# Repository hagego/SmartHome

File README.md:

# SmartHome
Tools and applications for my simple, very heterogeneous smart home

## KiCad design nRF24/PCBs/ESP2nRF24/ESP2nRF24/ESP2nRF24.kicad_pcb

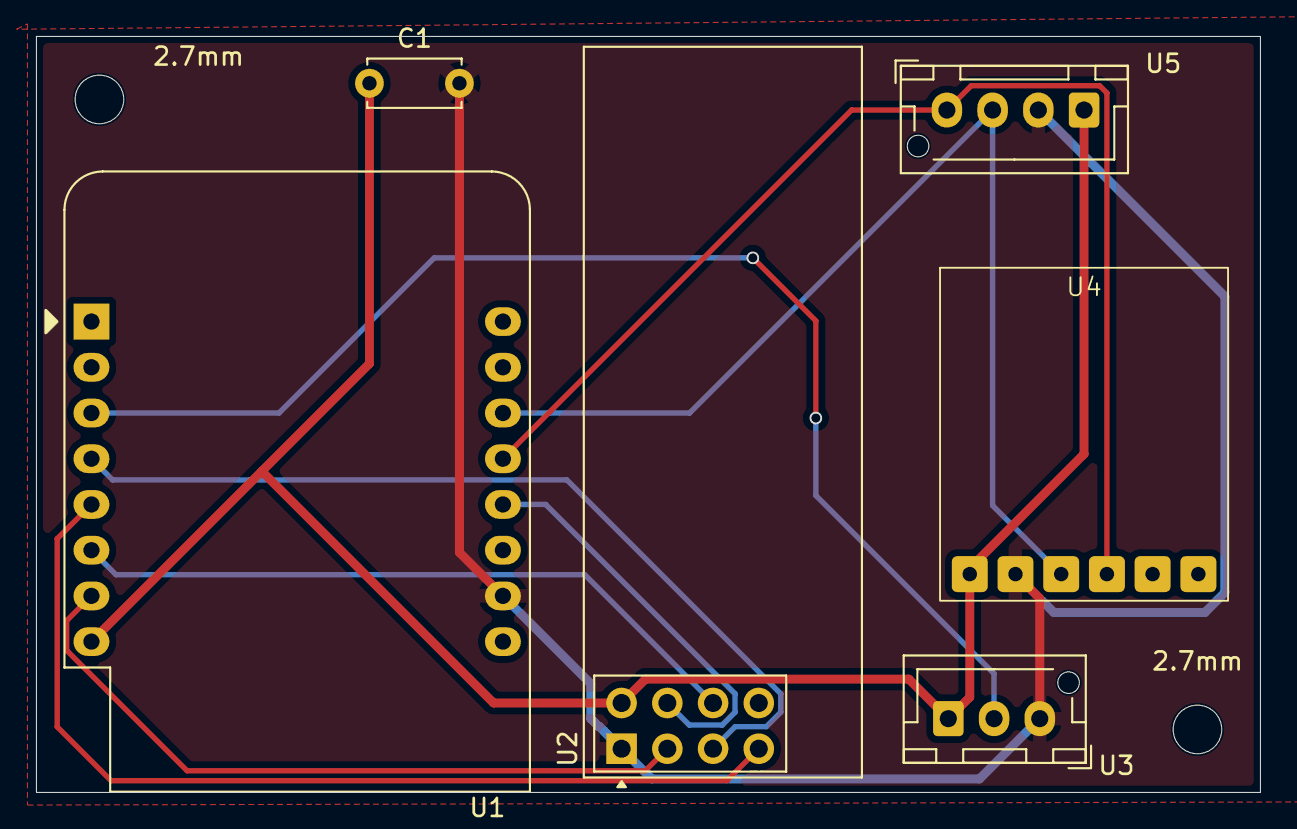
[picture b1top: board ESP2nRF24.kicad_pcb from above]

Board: 2 copper layers, 68.0 x 42.0 mm, 8 parts (0 on the bottom side), 10 nets.

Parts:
2.7mm, 2.7mm#2: MountingHole_2.7mm_M2.5
C1: 4.4uF; C_Disc_D5.0mm_W2.5mm_P5.00mm
U1: WEMOS_D1_mini; ESP8266 Mini USB-C
U2: NRF24L01_Breakout; nRF24L01_Breakout_extAntenna
U3: AM312; JST_XH_1x03_P2.54
U4: BE680; BME680
U5: BH1750; JST_XH_1x04_P2.54

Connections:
GND: C1.2, U1.10 (GND), U2.1 (GND), U3.3 (GND), U4.2 (GND), U5.2 (GND)
unnamed: C1.1, U1.8 (3V3), U2.2 (VCC), U3.1 (VCC), U4.1 (VCC), U5.1 (VCC)
unnamed: U1.7 (CS/D8), U2.3 (CE)
unnamed: U1.3 (D0), U3.2 (VOUT)
unnamed: U1.12 (D3), U2.4 (~CSN)
unnamed: U1.5 (MISO/D6), U2.7 (MISO)
unnamed: U1.6 (MOSI/D7), U2.6 (MOSI)
unnamed: U1.4 (SCK/D5), U2.5 (SCK)
unnamed: U1.14 (SCL/D1), U4.3 (SCL), U5.3 (SCL)
unnamed: U1.13 (SDA/D2), U4.4 (SDA), U5.4 (SDA)

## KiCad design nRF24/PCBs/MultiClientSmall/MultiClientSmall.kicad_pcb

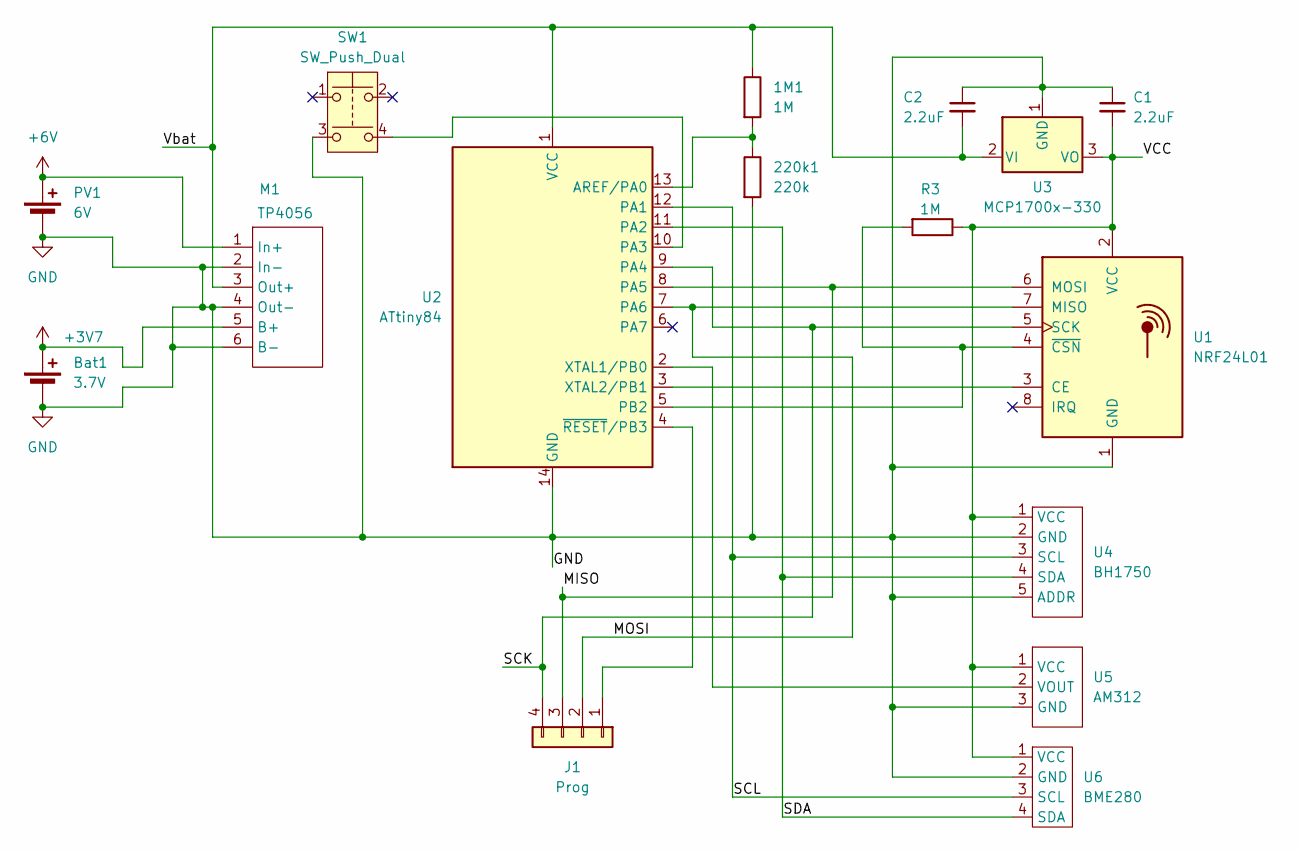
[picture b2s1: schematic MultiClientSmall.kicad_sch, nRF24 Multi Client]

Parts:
1M1: 1M; R_Axial_DIN0207_L6.3mm_D2.5mm_P10.16mm_Horizontal
220k1: 220k; R_Axial_DIN0207_L6.3mm_D2.5mm_P10.16mm_Horizontal
Bat1: 3.7V; JST_PH_1x02_P2.00
C1, C2: 2.2uF; C_Disc_D5.0mm_W2.5mm_P5.00mm
J1: Prog; PinHeader_1x04_P2.54mm_Vertical
M1: TP4056; TP4056-18650
PV1: 6V; JST_PH_1x02_P2.00
R3: 1M; R_Axial_DIN0207_L6.3mm_D2.5mm_P10.16mm_Horizontal
SW1: SW_Push_Dual; Push_E-Switch_KS01Q01
U1: NRF24L01; nRF24L01_Breakout
U2: ATtiny84; DIP-14_W7.62mm_Socket
U3: MCP1700x-330; TO-92_HandSolder
U4: BH1750
U5: AM312
U6: BME280

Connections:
+3V7: Bat1.1 (+), M1.5 (B+)
+6V: M1.1 (In+), PV1.1 (+)
/MISO: J1.3, U1.6 (MOSI), U2.8 (PA5)
/MOSI: J1.2, U1.7 (MISO), U2.7 (PA6)
/SCK: J1.4, U1.5 (SCK), U2.9 (PA4)
/SCL: U2.12 (PA1), U4.3 (SCL), U6.3 (SCL)
/SDA: U2.11 (PA2), U4.4 (SDA), U6.4 (SDA)
/VCC: C1.2, R3.1, U1.2 (VCC), U3.3 (VO), U4.1 (VCC), U5.1 (VCC), U6.1 (VCC); also elsewhere on the board
/Vbat: 1M1.1, C2.2, M1.3 (Out+), U2.1 (VCC), U3.2 (VI)
GND: 220k1.2, Bat1.2 (-), C1.1, C2.1, M1.2 (In-), M1.4 (Out-), M1.6 (B-), PV1.2 (-), SW1.3, U1.1 (GND), U2.14 (GND), U3.1 (GND), U4.2 (GND), U4.5 (ADDR), U5.3 (GND), U6.2 (GND)
unnamed: J1.1, U2.4 (~RESET/PB3)
unnamed: U1.3 (CE), U2.3 (XTAL2/PB1)
unnamed 12: R3.2, U1.4 (~CSN), U2.5 (PB2); also elsewhere on the board
unnamed: 1M1.2, 220k1.1, U2.13 (AREF/PA0)
unnamed: SW1.4, U2.10 (PA3)
unnamed: U2.2 (XTAL1/PB0), U5.2 (VOUT)

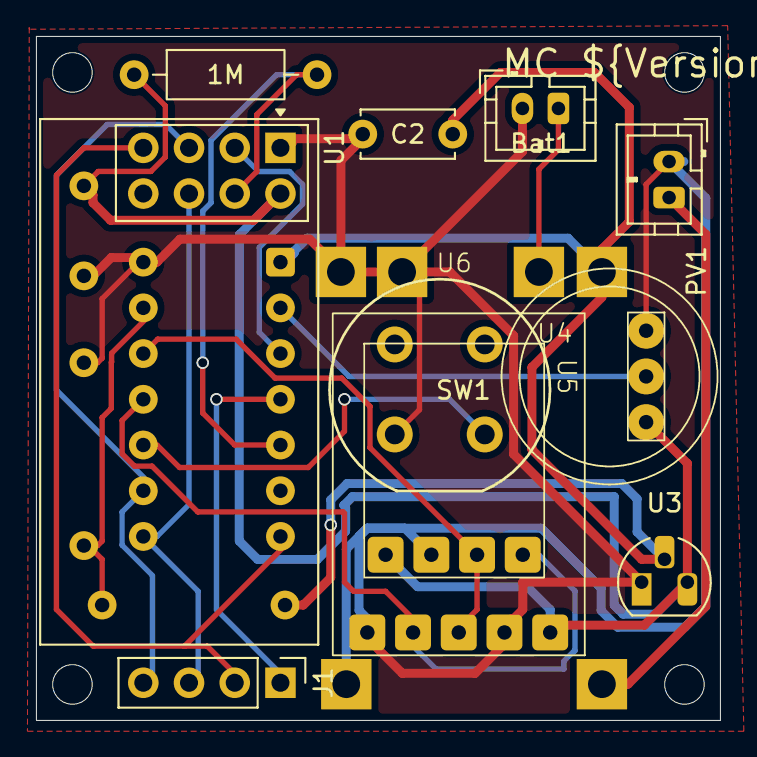
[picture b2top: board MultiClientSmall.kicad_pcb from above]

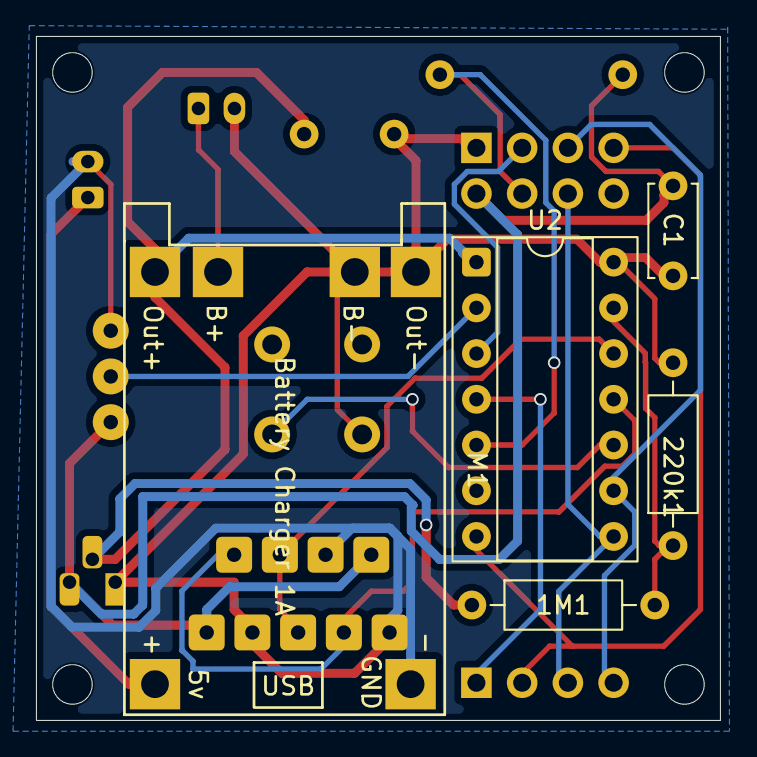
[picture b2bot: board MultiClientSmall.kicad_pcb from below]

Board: 2 copper layers, 38.0 x 38.0 mm, 16 parts (5 on the bottom side), 16 nets.

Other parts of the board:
1M: 1M; R_Axial_DIN0207_L6.3mm_D2.5mm_P10.16mm_Horizontal

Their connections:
/VCC: 1M.1; also elsewhere on the board
unnamed 12: 1M.2; also elsewhere on the board

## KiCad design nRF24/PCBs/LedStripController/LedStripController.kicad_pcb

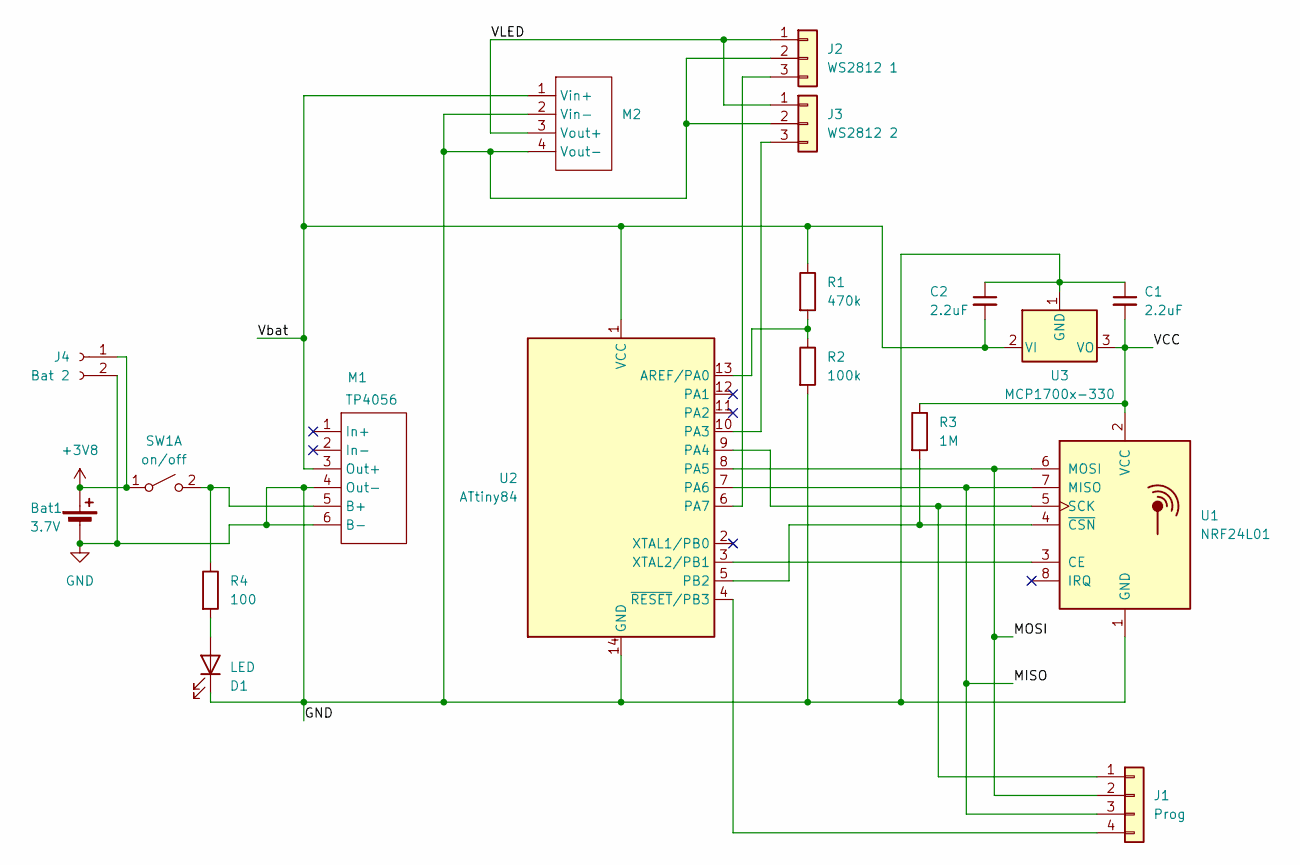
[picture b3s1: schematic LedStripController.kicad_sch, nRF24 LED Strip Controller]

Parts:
Bat1: 3.7V; JST_PH_1x02_P2.00
C1, C2: 2.2uF; C_Disc_D5.0mm_W2.5mm_P5.00mm
D1: LED; LED_D3.0mm
J1: Prog; PinHeader_1x04_P2.54mm_Vertical
J2: WS2812 1; JST_XH_1x03_P2.54
J3: WS2812 2; JST_XH_1x03_P2.54
J4: Bat 2; JST_XH_1x02_P2.54
M1: TP4056; TP4056-18650
M2: MT3608_Module
R1: 470k; R_Axial_DIN0207_L6.3mm_D2.5mm_P10.16mm_Horizontal
R2: 100k; R_Axial_DIN0207_L6.3mm_D2.5mm_P10.16mm_Horizontal
R3: 1M; R_Axial_DIN0207_L6.3mm_D2.5mm_P10.16mm_Horizontal
R4: 100; R_Axial_DIN0207_L6.3mm_D2.5mm_P10.16mm_Horizontal
SW1: on/off; SwitchHorizontal_SK-12F14
U1: NRF24L01; nRF24L01_Breakout
U2: ATtiny84; DIP-14_W7.62mm
U3: MCP1700x-330; TO-92_HandSolder

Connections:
+3V8: Bat1.1 (+), J4.1, SW1.1 (A); also elsewhere on the board
/MISO: J1.3, U1.7 (MISO), U2.7 (PA6)
/MOSI: J1.2, U1.6 (MOSI), U2.8 (PA5)
/VCC: C1.2, R3.1, U1.2 (VCC), U3.3 (VO)
/VLED: J2.1, J3.1, M2.3 (Vout+)
/Vbat: C2.2, M1.3 (Out+), M2.1 (Vin+), R1.1, U2.1 (VCC), U3.2 (VI)
GND: Bat1.2 (-), C1.1, C2.1, D1.1 (K), J2.2, J3.2, J4.2, M1.4 (Out-), M1.6 (B-), M2.2 (Vin-), M2.4 (Vout-), R2.2, U1.1 (GND), U2.14 (GND), U3.1 (GND); also elsewhere on the board
unnamed: D1.2 (A), R4.2
unnamed: J1.1, U1.5 (SCK), U2.9 (PA4)
unnamed: J1.4, U2.4 (~RESET/PB3)
unnamed: J2.3, U2.6 (PA7)
unnamed: J3.3, U2.10 (PA3)
unnamed: M1.5 (B+), R4.1, SW1.2 (B)
unnamed: U1.3 (CE), U2.3 (XTAL2/PB1)
unnamed: R3.2, U1.4 (~CSN), U2.5 (PB2)
unnamed: R1.2, R2.1, U2.13 (AREF/PA0)

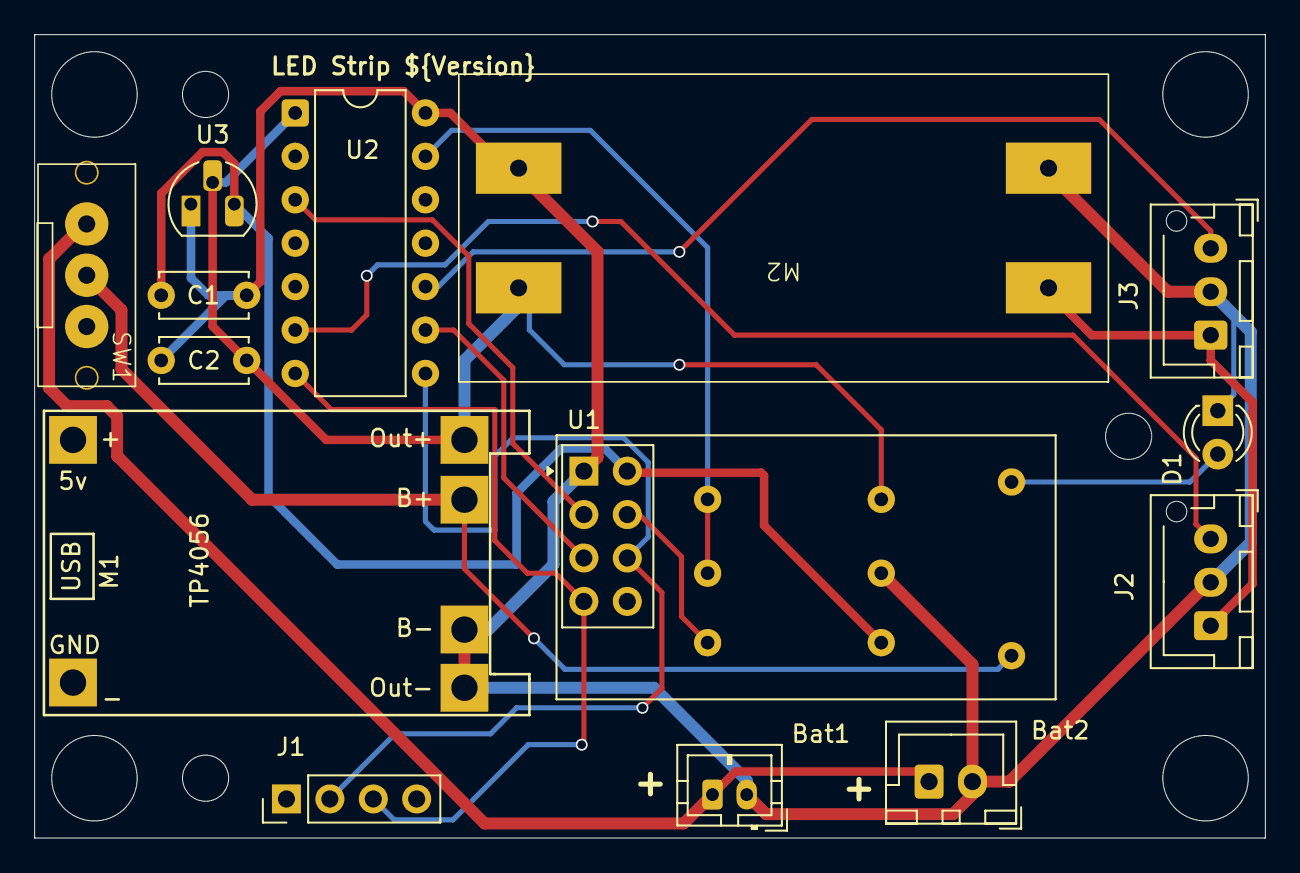
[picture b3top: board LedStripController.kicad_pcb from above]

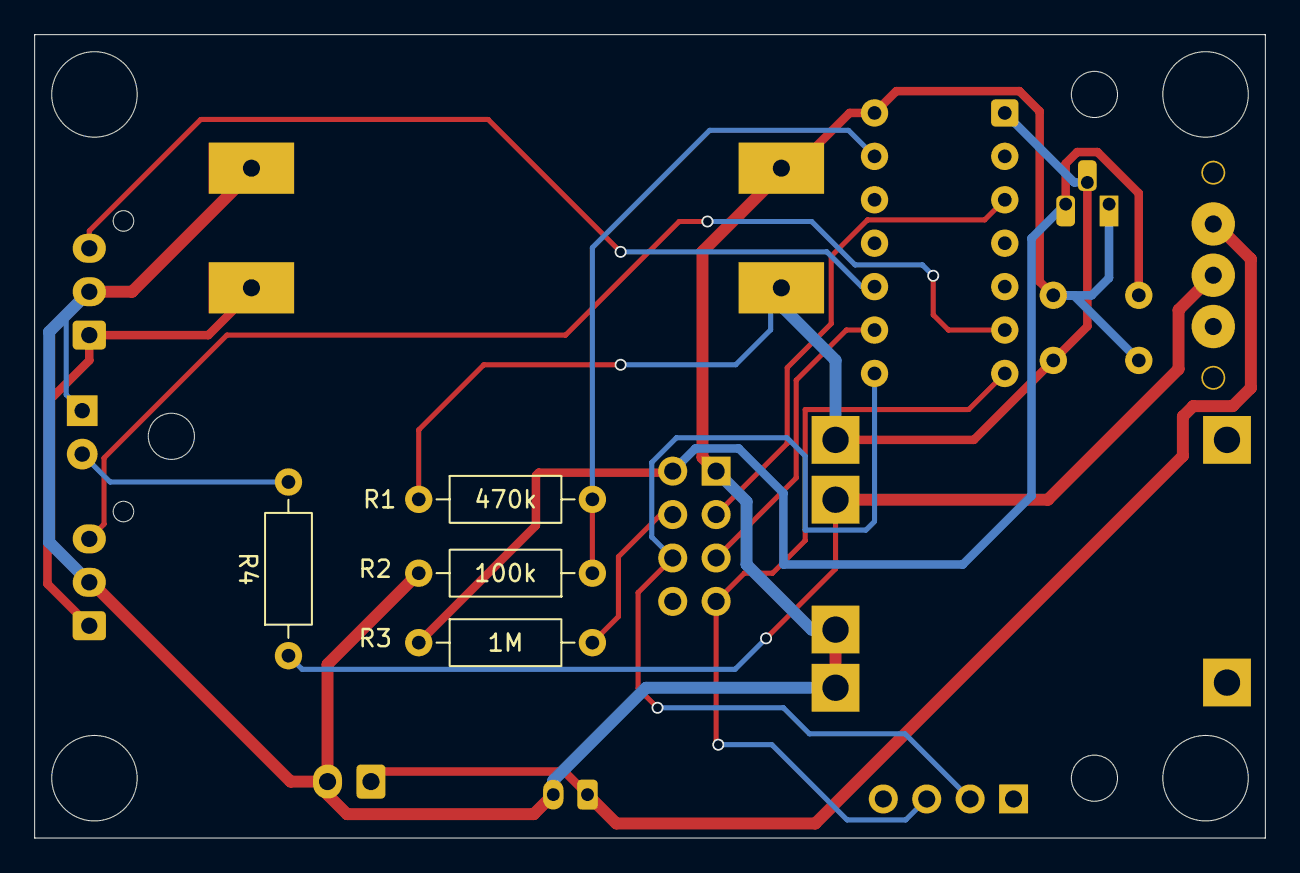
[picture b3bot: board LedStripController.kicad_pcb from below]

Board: 2 copper layers, 72.0 x 47.0 mm, 18 parts (4 on the bottom side), 16 nets.

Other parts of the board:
Bat2: Bat 2; JST_XH_1x02_P2.54

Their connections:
+3V8: Bat2.1; also elsewhere on the board
GND: Bat2.2; also elsewhere on the board

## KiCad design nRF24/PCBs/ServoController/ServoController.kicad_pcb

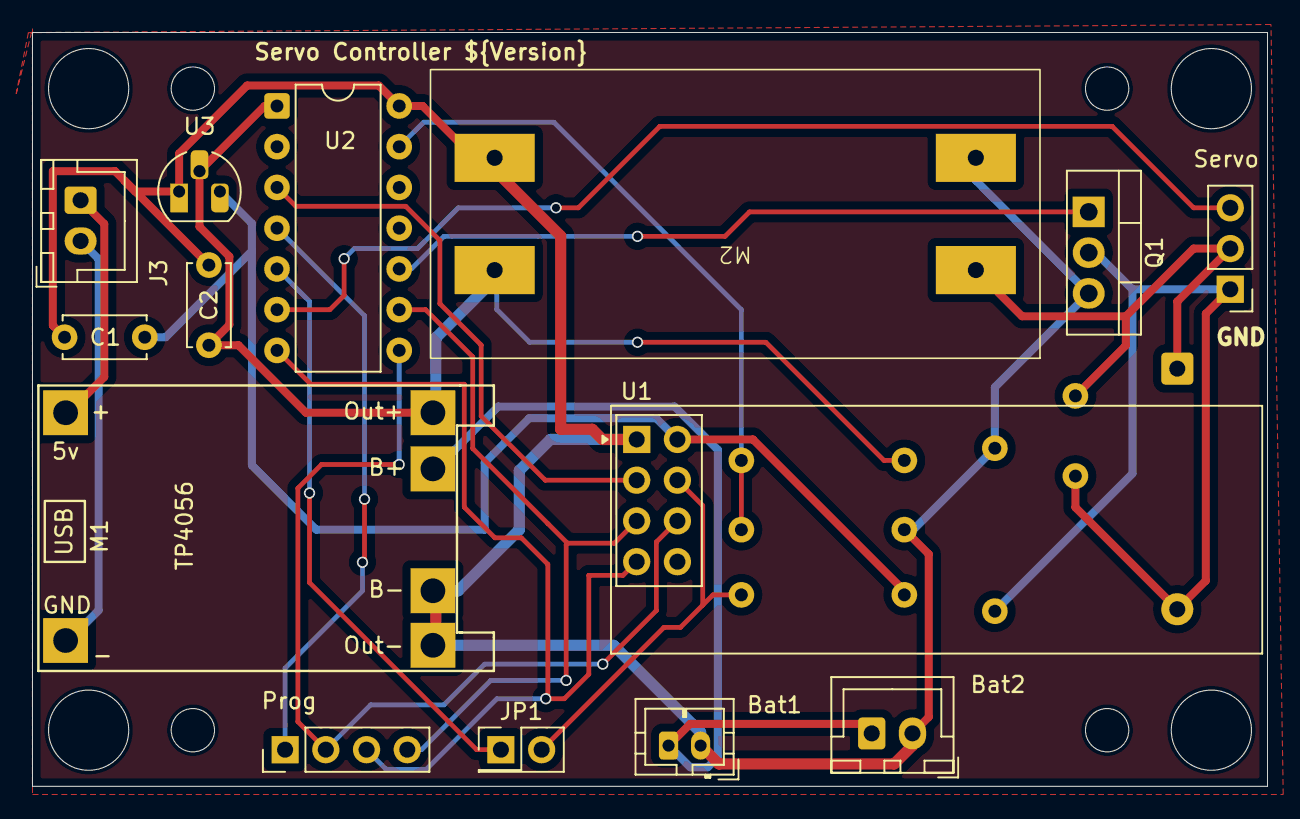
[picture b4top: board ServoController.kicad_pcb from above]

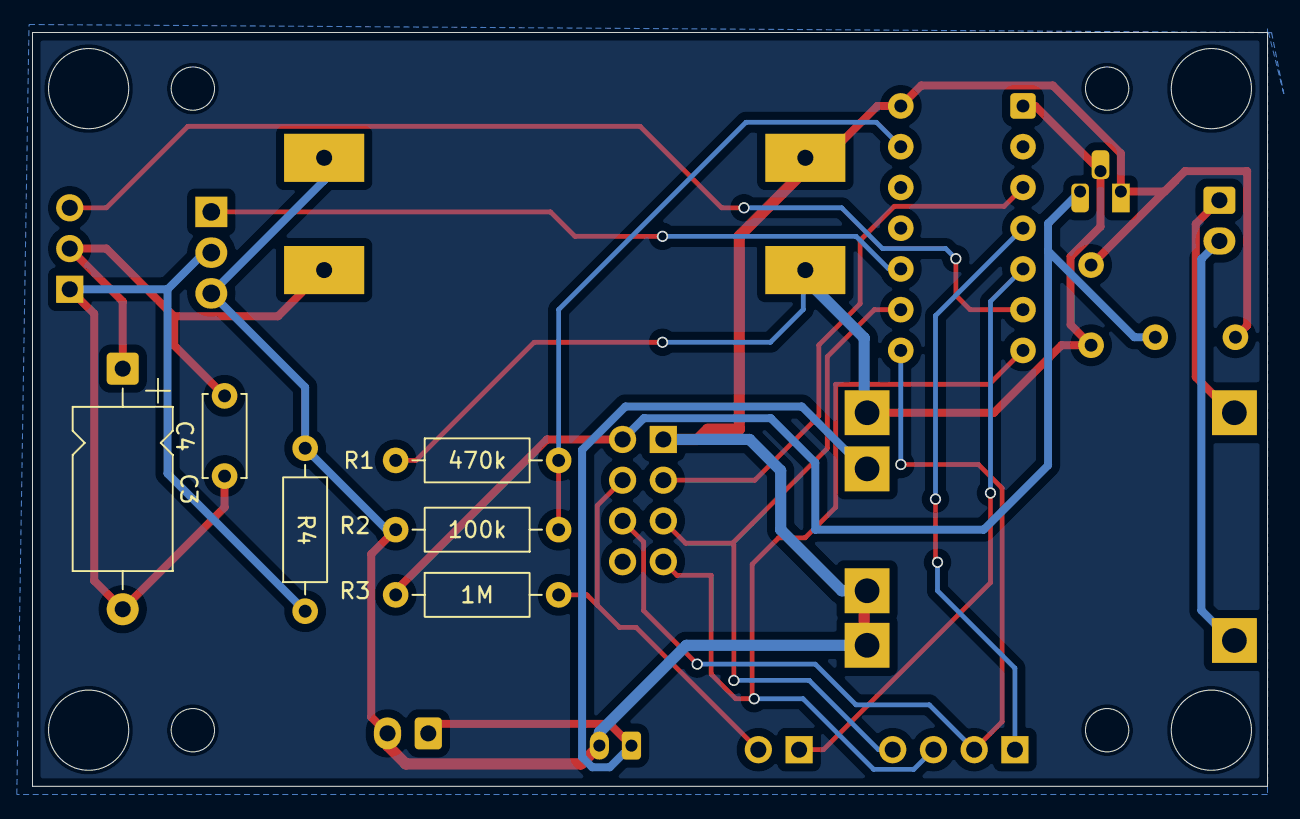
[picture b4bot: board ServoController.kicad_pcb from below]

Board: 2 copper layers, 77.0 x 47.0 mm, 20 parts (6 on the bottom side), 16 nets.

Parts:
Bat1: 3.7V; JST_PH_1x02_P2.00
Bat2: Bat2; JST_XH_1x02_P2.54
C1, C2: 2.2uF; C_Disc_D5.0mm_W2.5mm_P5.00mm
C3: 100uF; CP_Axial_L10.0mm_D6.0mm_P15.00mm_Horizontal
C4: 10uF; C_Disc_D5.0mm_W2.5mm_P5.00mm
J3: PV; JST_XH_1x02_P2.54
JP1: Jumper CSN; PinHeader_2x01_P2.54mm_Vertical
M1: TP4056; TP4056-18650
M2: MT3608_Module
Prog: Prog; PinHeader_1x04_P2.54mm_Vertical
Q1: IRL540N; TO-220-3_Vertical
R1: 470k; R_Axial_DIN0207_L6.3mm_D2.5mm_P10.16mm_Horizontal
R2: 100k; R_Axial_DIN0207_L6.3mm_D2.5mm_P10.16mm_Horizontal
R3, R4: 1M; R_Axial_DIN0207_L6.3mm_D2.5mm_P10.16mm_Horizontal
Servo: Servo; PinHeader_1x03_P2.54mm_Vertical
U1: NRF24L01; nRF24L01_Breakout_extAntenna
U2: ATtiny84; DIP-14_W7.62mm
U3: MCP1700x-330; TO-92_HandSolder

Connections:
+3V8: Bat1.1 (+), Bat2.1, M1.5 (B+)
/MISO: Prog.3, U1.7 (MISO), U2.7 (PA6)
/MOSI: Prog.2, U1.6 (MOSI), U2.8 (PA5)
/VCC: C1.2, R3.1, U1.2 (VCC), U3.3 (VO)
/Vbat: C2.2, M1.3 (Out+), M2.1 (Vin+), R1.1, U2.1 (VCC), U3.2 (VI)
GND: Bat1.2 (-), Bat2.2, C1.1, C2.1, M1.4 (Out-), M1.6 (B-), M2.2 (Vin-), M2.4 (Vout-), Q1.3 (S), R2.2, R4.2, U1.1 (GND), U2.14 (GND), U3.1 (GND)
unnamed: Prog.1, U2.4 (~RESET/PB3)
unnamed: Prog.4, U1.5 (SCK), U2.9 (PA4)
unnamed: C3.2, C4.1, Q1.2 (D), R4.1, Servo.1
unnamed: C3.1, C4.2, M2.3 (Vout+), Servo.2
unnamed: Servo.3, U2.6 (PA7)
unnamed: JP1.1 (A), U2.5 (PB2)
unnamed: JP1.2 (B), R3.2, U1.4 (~CSN)
unnamed: Q1.1 (G), U2.10 (PA3)
unnamed: U1.3 (CE), U2.3 (XTAL2/PB1)
unnamed: R1.2, R2.1, U2.13 (AREF/PA0)

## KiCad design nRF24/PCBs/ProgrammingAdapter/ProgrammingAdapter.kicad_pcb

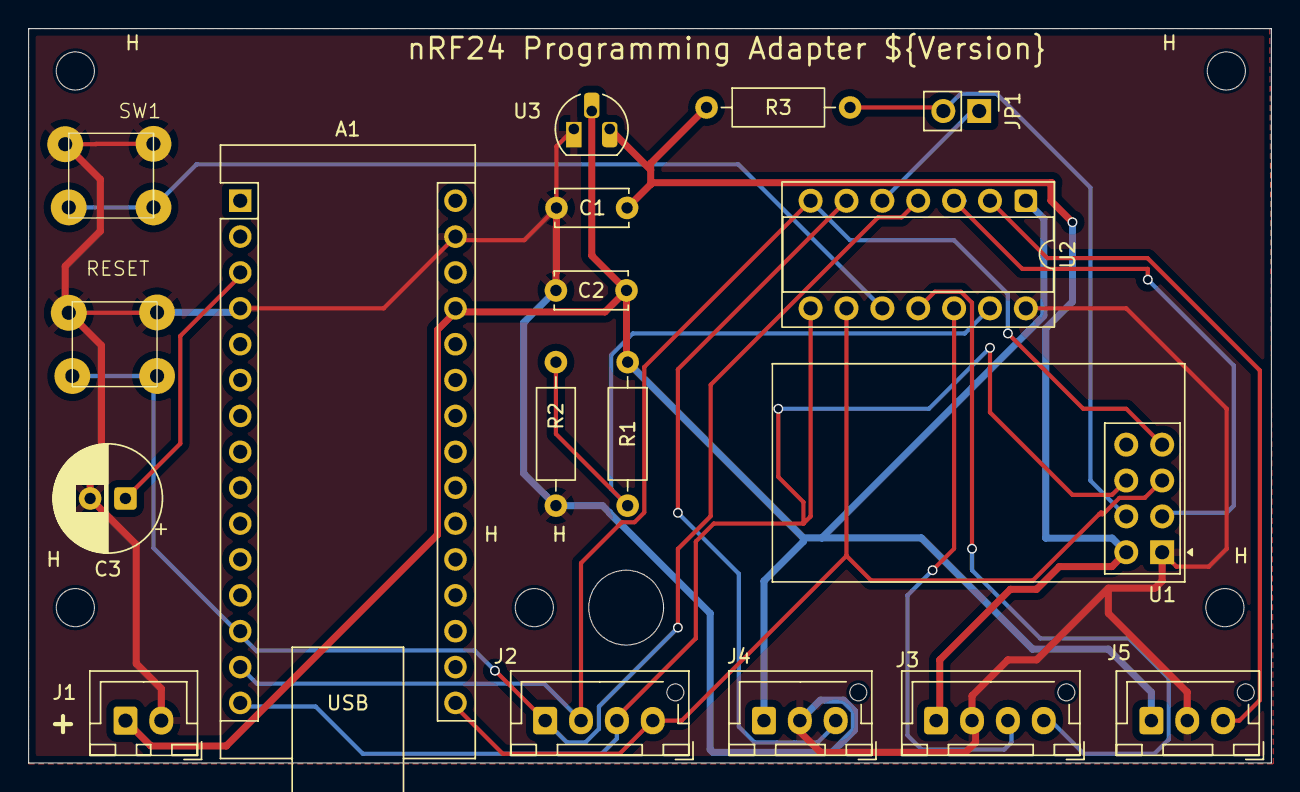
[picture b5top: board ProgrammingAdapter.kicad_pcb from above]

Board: 2 copper layers, 88.0 x 52.0 mm, 24 parts (0 on the bottom side), 16 nets.

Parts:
A1: Arduino_Nano_v3.x; Arduino_Nano
C1, C2: 2.2uF; C_Disc_D5.0mm_W2.5mm_P5.00mm
C3: 100uF; CP_Radial_D7.5mm_P2.50mm
H: M2.5; MountingHole_2.7mm_M2.5
H#2, H#3, H#4, H#6: M2.5; MountingHole_2.7mm_M2.5
H#5: M5; MountingHole_5.3mm_M5
J1: 5V Out; JST_XH_1x02_P2.54
J2: SPI Prog; JST_XH_1x04_P2.54
J3: IIC 3V3; JST_XH_1x04_P2.54
J4: WS2812; JST_XH_1x03_P2.54
J5: AM312; JST_XH_1x03_P2.54
JP1: CSN; PinHeader_1x02_P2.54mm_Vertical
R1: 470k; R_Axial_DIN0207_L6.3mm_D2.5mm_P10.16mm_Horizontal
R2: 100k; R_Axial_DIN0207_L6.3mm_D2.5mm_P10.16mm_Horizontal
R3: 1M; R_Axial_DIN0207_L6.3mm_D2.5mm_P10.16mm_Horizontal
RESET: RESET; Micro_Push_Button_6x6
SW1: PA3; Micro_Push_Button_6x6
U1: NRF24L01; nRF24L01_Breakout
U2: ATtiny84; Engineering_DIP14_Socket
U3: MCP1700x-330; TO-92_HandSolder

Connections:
/MISO: A1.15 (D12), J2.3, U1.6 (MOSI), U2.8 (PA5)
/MOSI: A1.14 (D11), J2.2, U1.7 (MISO), U2.7 (PA6)
/SCK: A1.16 (D13), J2.4, U1.5 (SCK), U2.9 (PA4)
/SCL: J3.3, U2.12 (PA1)
/SDA: J3.4, U2.11 (PA2)
/VCC: C1.2, J3.1, R3.1, U1.2 (VCC), U3.3 (VO)
/Vbat: A1.27 (+5V), C2.2, J1.1, J4.1, J5.1, R1.1, U2.1 (VCC), U3.2 (VI)
GND: A1.4 (GND), A1.29 (GND), C1.1, C2.1, C3.2, J1.2, J3.2, J4.2, J5.2, R2.2, RESET.1, RESET.2, SW1.1, SW1.2, U1.1 (GND), U2.14 (GND), U3.1 (GND)
unnamed: A1.13 (D10), J2.1, RESET.3 (K), RESET.4 (A), U2.4 (~RESET/PB3)
unnamed: A1.3 (~RESET), C3.1
unnamed: J4.3, U2.6 (PA7)
unnamed: JP1.1 (A), U2.5 (PB2)
unnamed: JP1.2 (B), R3.2, U1.4 (~CSN)
unnamed: SW1.3 (K), SW1.4 (A), U2.10 (PA3)
unnamed: U1.3 (CE), U2.3 (XTAL2/PB1)
unnamed: R1.2, R2.1, U2.13 (AREF/PA0)

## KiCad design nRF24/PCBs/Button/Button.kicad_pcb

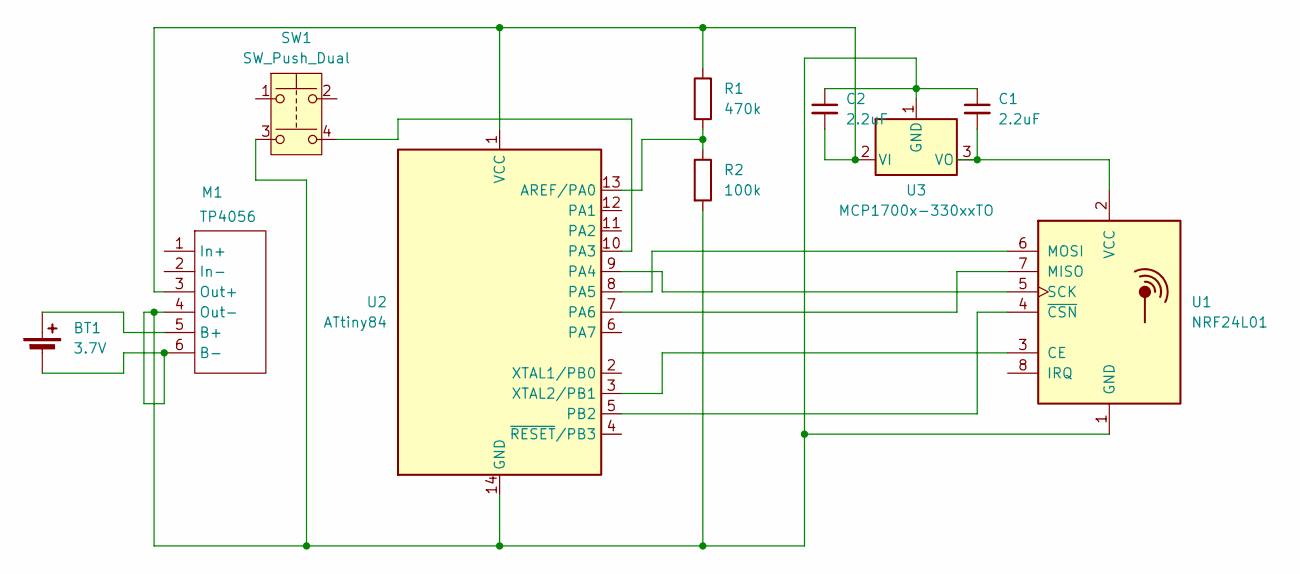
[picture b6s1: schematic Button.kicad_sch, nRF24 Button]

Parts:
BT1: 3.7V; JST_PH_B2B-PH-K_1x02_P2.00mm_Vertical
C1: 2.2uF; C_Disc_D5.0mm_W2.5mm_P5.00mm
C2: 2.2uF; C_Disc_D5.0mm_W2.5mm_P2.50mm
M1: TP4056; TP4056-18650
R1: 470k; R_Axial_DIN0207_L6.3mm_D2.5mm_P10.16mm_Horizontal
R2: 100k; R_Axial_DIN0207_L6.3mm_D2.5mm_P10.16mm_Horizontal
SW1: SW_Push_Dual; Push_E-Switch_KS01Q01
U1: NRF24L01; nRF24L01_Breakout
U2: ATtiny84; DIP-14_W7.62mm_Socket
U3: MCP1700x-330xxTO; TO-92_Inline

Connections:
unnamed: BT1.1 (+), M1.5 (B+)
unnamed: BT1.2 (-), C1.1, C2.1, M1.4 (Out-), M1.6 (B-), R2.2, SW1.3, U1.1 (GND), U2.14 (GND), U3.1 (GND)
unnamed: C2.2, M1.3 (Out+), R1.1, U2.1 (VCC), U3.2 (VI)
unnamed: U1.3 (CE), U2.3 (XTAL2/PB1)
unnamed: U1.7 (MISO), U2.7 (PA6)
unnamed: U1.6 (MOSI), U2.8 (PA5)
unnamed: U1.5 (SCK), U2.9 (PA4)
unnamed: C1.2, U1.2 (VCC), U3.3 (VO)
unnamed: U1.4 (~CSN), U2.5 (PB2)
unnamed: R1.2, R2.1, U2.13 (AREF/PA0)
unnamed: SW1.4, U2.10 (PA3)

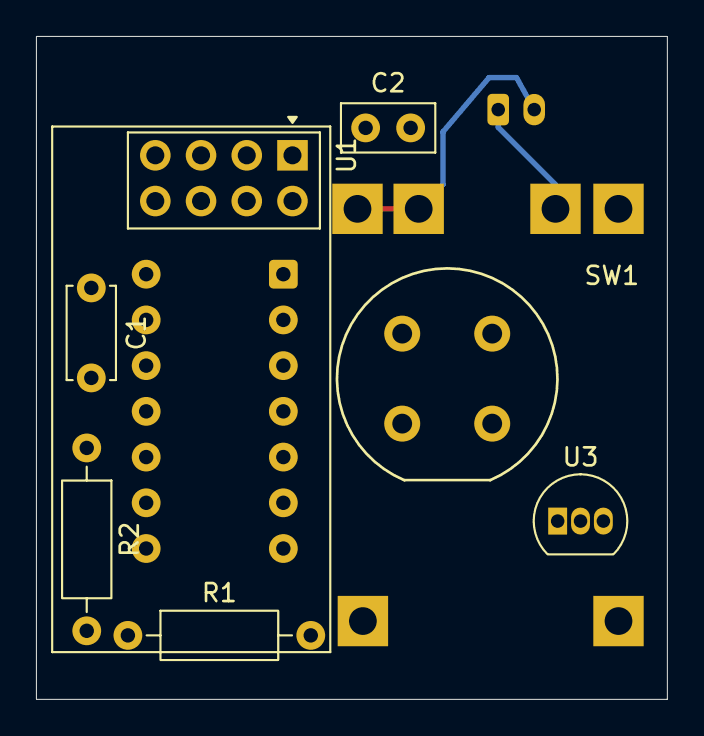
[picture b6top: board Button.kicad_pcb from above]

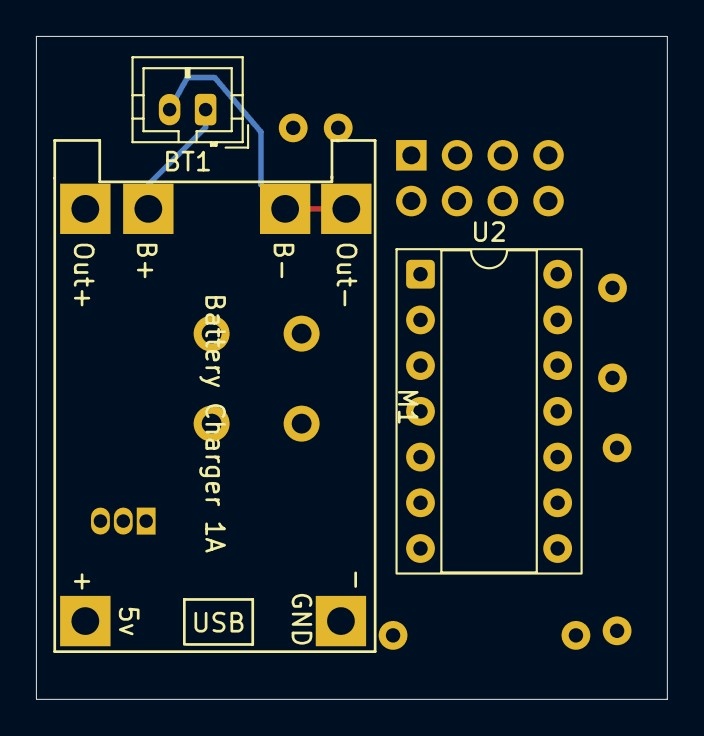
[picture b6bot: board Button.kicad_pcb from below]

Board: 2 copper layers, 35.1 x 36.8 mm, 10 parts (3 on the bottom side), 11 nets.

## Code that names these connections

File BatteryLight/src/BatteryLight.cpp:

/**
 * BatteryLight - Battery-powered light with motion sensor
 * Uses ATtiny84, PIR motion sensor, and LED driver with PWM brightness control
 * ATtiny84 pinout:
 * - pin  2: PB0,PCINT8  - Motion sensor 1 input (with pull-up resistor)
 * - pin  3: PB1         - CE for nRF24L01
 * - pin  4: PB3,PCINT11 - Motion sensor 2 input (with pull-up resistor) - requires fusing PB3 as GPIO
 * - pin  5: PB2         - CS for nRF24L01
 * - pin  6: PA7,OC0B    - PWM output to LED driver
 * - pin  7: PA6,MOSI    - SPI MOSI for nRF24LO1
 * - pin  8: PA5,MISO    - SPI MISO for nRF24LO1
 * - pin  9: PA4,SCK     - SPI SCK for nRF24LO1
 * - pin 10: PA3         - DCDC enable for LED driver
 * - pin 11: PA2         - IIC SDA for BH1750FVI
 * - pin 12: PA1         - IIC SCL for BH1750FVI
 * - pin 13: PA0,ADC0    - Battery voltage measurement
 */


#include <Arduino.h>

#include <avr/sleep.h>
#include <avr/interrupt.h>

#include <SPI.h>
#include <nRF24L01.h>
#include <RF24.h>

// nRF24 address to use (channel) (5 bytes)
const byte nRF24Address[6] = "1clnt";
//const byte nRF24Address[6] = "debug";

// global RF24 object
RF24          radio(PB1, PB2);  // create a global RF24 object, CE, CSN

void enterSleep() {
  GIMSK  |= _BV(PCIE1);                  // Enable Pin Change Interrupts
  GIMSK  |= _BV(PCIE0);                  // Enable Pin Change Interrupts
 
  PCMSK1 |= _BV(PCINT8);            // Enable pin change interrupt on PIN_MOTION1

  
  set_sleep_mode(SLEEP_MODE_PWR_DOWN);   // replaces above statement
  sleep_enable();                        // Sets the Sleep Enable bit in the MCUCR Register (SE BIT)
  sei();                    // nRF24 address to use (channel) (5 bytes)
  sleep_cpu();                           // sleep
  // The CPU is now sleeping, and will wake up on interrupt
  // The ISR will be called when the interrupt occurs
  // The CPU will wake up and continue executing from here after ISR
  //cli();                                 // Disable interrupts
  GIMSK  &= ~_BV(PCIE1);                 // Disable Pin Change Interrupts
  GIMSK  &= ~_BV(PCIE0);                 // Disable Pin Change Interrupts

  PCMSK1 &= ~_BV(PCINT8); 

  sleep_disable();                       // Disable sleep mode
}

// ISR for motion sensor (pin change)
ISR (PCINT0_vect) {  
}
ISR (PCINT1_vect) {  
}

// ISR for bad interrupt
// This is a catch-all for any interrupts that don't have a specific handler
ISR(BADISR_vect) {
}

/**
 * Initialize PWM for PA7 (ATtiny84 pin 6), connected to OC0B (Output Compare B for 8-bit Timer0)
 */
void initPWM() {
  DDRA |= _BV(PA7);                      // Set PA7 as output

  // configure timer control
  TCCR0A = _BV(WGM00)  | _BV(WGM01) |    // Fast PWM mode with TOP = OxFF
           _BV(COM0B0) |_BV(COM0B1);     // set OC0B on compare match, clear at BOTTOM (inverted PWM)

  TCCR0B = _BV(CS01);                    // Prescaler = 8
           
  OCR0B = 0;                             // Initial duty cycle = 0%
}

/**
 * Set PWM duty cycle on PA7
 * @param dutyCycle Value from 0 to 100 representing duty cycle percentage
 */
void setPWMDutyCycle(uint8_t dutyCycle) {
  if (dutyCycle > 100) dutyCycle = 100;
  
  // Calculate the compare value based on duty cycle
  uint8_t compareValue = (uint8_t)(((double)dutyCycle/100.0)*255.0);
  OCR0B = compareValue;
}

void setup() {

  /**
 * pinout:
 * - pin  2: PB0,PCINT8  - Motion sensor 1 input (with pull-up resistor)
 * - pin  3: PB1         - CE for nRF24L01
 * - pin  4: PB3,PCINT11 - Motion sensor 2 input (with pull-up resistor) - requires fusing PB3 as GPIO
 * - pin  5: PB2         - CS for nRF24L01
 * - pin  6: PA7,OC0B    - PWM output to LED driver
 * - pin  7: PA6,MOSI    - SPI MOSI for nRF24LO1
 * - pin  8: PA5,MISO    - SPI MISO for nRF24LO1
 * - pin  9: PA4,SCK     - SPI SCK for nRF24LO1
 * - pin 10: PA3         - DCDC enable for LED driver
 * - pin 11: PA2         - IIC SDA for BH1750FVI
 * - pin 12: PA1         - IIC SCL for BH1750FVI
 * - pin 13: PA0,ADC0    - Battery voltage measurement
 */

  DDRB  &= ~_BV(PB0);            // Set PB0 as input: motion sensor 1
  PORTB |=  _BV(PB0);            // Enable pull-up resistor on PB0
  //DDRB  |=  _BV(PB1);            // Set PB1 as output: CE for nRF24L01
  DDRB  &= ~_BV(PB3);            // Set PB3 as input: motion sensor 2
  PORTB |=  _BV(PB3);            // Enable pull-up resistor on PB3
  //DDRB  |=  _BV(PB2);            // Set PB2 as output: CS for nRF24L01
  DDRA  |=  _BV(PA7);            // Set PA7 as output: LED driver PWM control

  DDRA  |=  _BV(PA3);            // Set PA3 as output: enables DCDC for LED driver

  radio.begin();

  radio.stopListening();          // set module as transmitter
  radio.setAutoAck(1);            // Ensure autoACK is enabled
  radio.setRetries(5,15);         // Max delay between retries & number of retries
  radio.setPayloadSize(16);       // Set payload size to 16 bytes
  radio.setPALevel(RF24_PA_HIGH); // Set power level to high
  radio.openWritingPipe(nRF24Address); // Write to device address 

  // send connect message
  char buffer[10] = "C:1";
  radio.write( buffer,sizeof(buffer) );
  radio.txStandBy();              // Wait for the transmission to complete


  // disable DCDC for LED driver and wait 5 seconds
  PORTA &= ~_BV(PA3);            // Set PA3 low: disables DCDC for LED driver
}

void loop() {

  enterSleep();

  radio.powerUp();                       // Power up the radio

    // send connect message
  char buffer[10] = "M:1";
  radio.write( buffer,strlen(buffer) );
  radio.txStandBy();              // Wait for the transmission to complete

    // enable DCDC and initialize PWM
  PORTA |= _BV(PA3);            // Set PA3 high: enables DCDC for LED driver
  initPWM();


  // Fade in: Increase duty cycle from 0% to 100%
  for (uint8_t dutyCycle = 0; dutyCycle <= 50; dutyCycle += 5) {
    setPWMDutyCycle(dutyCycle);
    delay(100);
  }
  
  delay(1000);
  
  // // Fade out: Decrease duty cycle from 100% to 0%
  for (uint8_t dutyCycle = 50; dutyCycle > 0; dutyCycle -= 5) {
    setPWMDutyCycle(dutyCycle);
    delay(100);
  }

  delay(1000);
}

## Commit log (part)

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2016-12-30 initial version of MoteinoServer on GitHub
2016-12-30 reorganized .gitignore
2016-12-30 fixed working directory in moteinoserver.service
2016-12-31 fixed bug, adding missing '/' for config directory
2017-12-25 now also allowing long clicks
2018-01-01 added (old) Arduino based FS20 shutter control for openhab
    added (old) Arduino based FS20 shutter control for openhab
2018-01-06 Inital trial version of RabbitHatchDoordelay
    Inital trial version of RabbitHatchDoordelay
2018-01-08 First working version using MQTT
    First working version using MQTT
2018-03-25 first working version including DHT22 temperature measurement
2018-04-01 added possibility to change open/close angles thru MQTT
2018-04-08 Verion 1.0
2019-12-21 migrated Moteino Server from using a ctp client to MQTT
2019-12-25 initial version
2019-12-25 removed PhoneFinder again
2020-04-13 Created GarageDoor ESP8266 project
2020-05-01 adding relay control
2020-05-21 Initial Version
    Initial Version
2020-05-23 added power-on default and timeout
2020-06-05 Created PCB using Fritzing
2020-06-05 moved docs into Doc folder
2020-06-14 updated RabbitHutchDoor Fritzing layout, minor changes in code
2020-09-12 added rabbitfeeder
2020-10-04 bugfix: Supply correct client name during reconnect
2020-10-25 Added servo power down in RabbitFeeder
2020-10-25 Connected DHT11 to switched GND for power saving
2020-11-01 added voltage divider to VBAT to measure battery voltage
2020-11-08 added battery voltage monitoring, disabled temperature measurement
2020-11-14 bugfixes, added picture of assembled board
2020-12-18 Started RemoteControl project
2020-12-20 commit test from new PC
2020-12-20 commit test 2 from new PC
2020-12-22 first usable version of RemoteControl, validated using ESP D1 Mini
2020-12-25 fixed PCB errors and changed Attiny85 code to using gpio5/pin1
2020-12-26 fix ro set to always set to idle mode again
2021-01-09 1st version of FS20 MQTT, updates on Remote Control
2021-01-10 1st productive version of FS20 MQTT
2021-01-18 fixed short on IRL540N
2022-03-26 added CO Sensor and GarageDoor FingerprintSensor
2024-09-28 updated RabbitHutchDoor
2024-11-10 continued work on new version of rabbit hutch door
2024-11-17 new version of rabbithutchdoor
2025-01-02 updated rabbit hatch door
2025-01-25 added MotionSensor
2025-01-25 bugfix MotionSensor
2025-02-11 finalized motion sensor
2025-03-05 finalied brightnesschecker
2025-04-06 added UniversalServoSensor project
2025-04-20 removed C Servo from UniversalSensorPV PCB
2025-05-10 nRF24 based motion detection
2025-05-30 first version of ATtiny84 + nRF24LO1 Motion Detection Sensor
2025-06-06 added BME680 readout
2025-06-06 fixed motion sensor MQTT topic name
2025-06-18 Finalized UniversalServoSensor
2025-06-19 finalized nRF24 Receiver incl. local sensor
2025-06-19 ATtiny ISP programmer using Arduino nano
2025-06-30 Finalized nRF24 motion sensor
2025-07-05 Fixes to nRF24 receiver
2025-07-05 Initial version of EspSender
2025-07-05 Deleted MoteinoServer
2025-07-05 Deleted FS20 Shutter Control
2025-07-05 Moved nRF24 project PCBs into separate folder
2025-08-11 Added Environmental sensor
2025-08-20 updated nRF24 motion sensor to 3 inputs
2025-08-27 Deleted old rabbithutchdiir and Garage Oopener projects
2025-08-31 rst version of garage door server with NFC reader
2025-08-31 global .gitignore changes
2025-08-31 garagedoorserver bugfix
2025-08-31 added garage opener as motionsensor 3 to nRF24 motion sensor
2025-09-13 added back PCB drawings zu UnoiversalServoSensor
2025-09-28 First draft versio of BatterLight
2025-10-03 Initial version of nRF24 EspRemoteControl
2025-10-03 added nRF24 to BatteryLight
2025-10-03 Bugfix in EspReceiver
2025-10-03 moved BatteryLight under nRF24 folder
2025-10-03 moved BatteryLight PCB drawing in right location
2025-10-04 moved BatteryLight.fz into right folder
2025-10-05 Continued BatteryLight
2025-10-12 continued Battery Light
2025-10-12 Continued Battery Light (PCB)
2025-10-17 Finalized Battery Light PCB
2025-10-21 Finalized Battery Light "offline coding"
2025-10-24 Continued EspRemoteControl
2025-10-24 Battery Light and LED Strip PCBs
2025-10-25 Adopted Battery Light to 8MHz clock
2025-10-25 added LED Strip support to BatteryLight
2025-10-26 Continued work on LED strip
2025-10-31 renamed BatteryLight to LedController
2025-11-01 LedController with hp_BH1750 library
2025-11-02 Working version of LedController with downstripped BH1750 library
2025-11-08 first complete LedStrip PCB
2025-11-08 nRF254 LED Strip PCB order
2025-11-08 renamed EspRemoteControl to Controller
2025-11-10 working version of nRF24 LED Controller portable
2025-11-12 LED Strip PCB manufacturing version
2025-11-16 added ack payloads to nRF24 code
2025-11-22 added motion sensor to LED Controller, started Free Cad
2025-11-23 working Led Controller as motino sensor only
2025-11-23 renamed to Controller.cpp
2025-11-27 removed obsolete nRF24 EspReceiver and MotionSensor
2025-11-30 Temperature Sensor PCB production version
2025-11-30 continued Battery Light PCB & housing
2025-11-30 WS2812 pattern shift at L command
2025-12-07 Battery Light PCB 1.2
2025-12-07 nRF24 Controller continued
2025-12-07 LedController ready for test
2025-12-07 added Battery Light housing cover
2025-12-10 Completed cover of Battery Light housing
2025-12-13 first version of BME280 sensor
2025-12-14 nRF24 temperature sensor ready for test
2025-12-14 Temperature Sensor PCB V1.1
2025-12-19 Motion Sensor PCB: connected grounds
2025-12-19 Temperature Sensor PCB: Fixed resistor values
2025-12-19 Started nRF24 Button PCB with KiCad
2025-12-20 Continued Temperature Sensor Housing
2025-12-20 renamed FreeCad file Button to Temperature Sensor
2025-12-22 Created MultiClientSmall KiCAD Project
2025-12-22 Deleted KiCAD Button project
2025-12-22 nRF24 Controller bugfix: Only listen to pipe 1
2025-12-25 Production Version of nRF24 Multi Client Small
2025-12-26 Temperature Sensor Housing continued
2025-12-26 Started LED Strip Controller in KiCad
2025-12-26 nRF24 Client Production Version
2025-12-28 Bugfixes in nRF24 code
2025-12-28 Continued on housings
2025-12-28 Started Programming Adapter
2025-12-29 Added NFC Garage Door Oopener
2025-12-30 Battery Light housing as used at Wallbox
2025-12-30 LED Strip Controller and Programming Adapter WIP
2026-01-02 Moved all parameter to spreadsheet
2026-01-03 Programming Adapter production version 1.0
2026-01-03 Battery Light Wallbox production version
2026-01-16 Deleted nRF24 Multi Client Housing
2026-01-17 Version used byy Garage Door Opener
2026-01-17 Programming Adapter changes after first usage
2026-01-17 nRF24 Multi Client changes after first usage
2026-01-18 nRF24 client code Slee for all types
2026-01-18 nRF24 Multi CLient PCB
2026-01-19 LED Strip Coller WIP
2026-01-19 nRF24 Controller WIP
2026-02-13 nRF24 client fixes
2026-02-14 Fixed AM312 motion sensor orientation
2026-02-15 nRF24 Client: Motion Sensor UG installed
2026-02-17 LED Strip Controller production version
2026-02-18 nRF24 client code updates
2026-02-18 Battery Light PCB update
2026-02-22 nRF24 client: improved motion detection battery life, less radio wakeups
2026-03-04 added nRF24 Servo Controller PCB
2026-03-09 Added ESP8266 (D1 mini) to nRF24 gateway
2026-03-11 added watchdog to garage door server
2026-03-21 added PCB size to ESP2nRF24
2026-03-26 nRF24 Controller: Added OTA Update and setting of TX Power
2026-03-28 nRF24 Controller: Added programmable TX Power Level
2026-03-29 Update KiCad 10
2026-04-06 nRF24 Client Cleanups
2026-04-06 updates to new KiCad version
2026-04-06 nRF24 Controller fixes
2026-04-06 nRF24 improvements
2026-04-12 nRF24 LED Strip Controller Debugging
2026-05-03 nRF24 client power optimizations
2026-05-31 nRF24 client battery measurement optimization
2026-05-31 Renamed LedController.cpp to UniversalClient.cpp
2026-05-31 renamed LedController to UniversalCLient
2026-05-31 nRF24 Universal CLient Rev 1
2026-05-31 nRF24 PCB changes
2026-06-21 nRF24 Client bugfix for Button, increased REV to 2
2026-06-27 nRF24 Multi-Client PCB V1.3
